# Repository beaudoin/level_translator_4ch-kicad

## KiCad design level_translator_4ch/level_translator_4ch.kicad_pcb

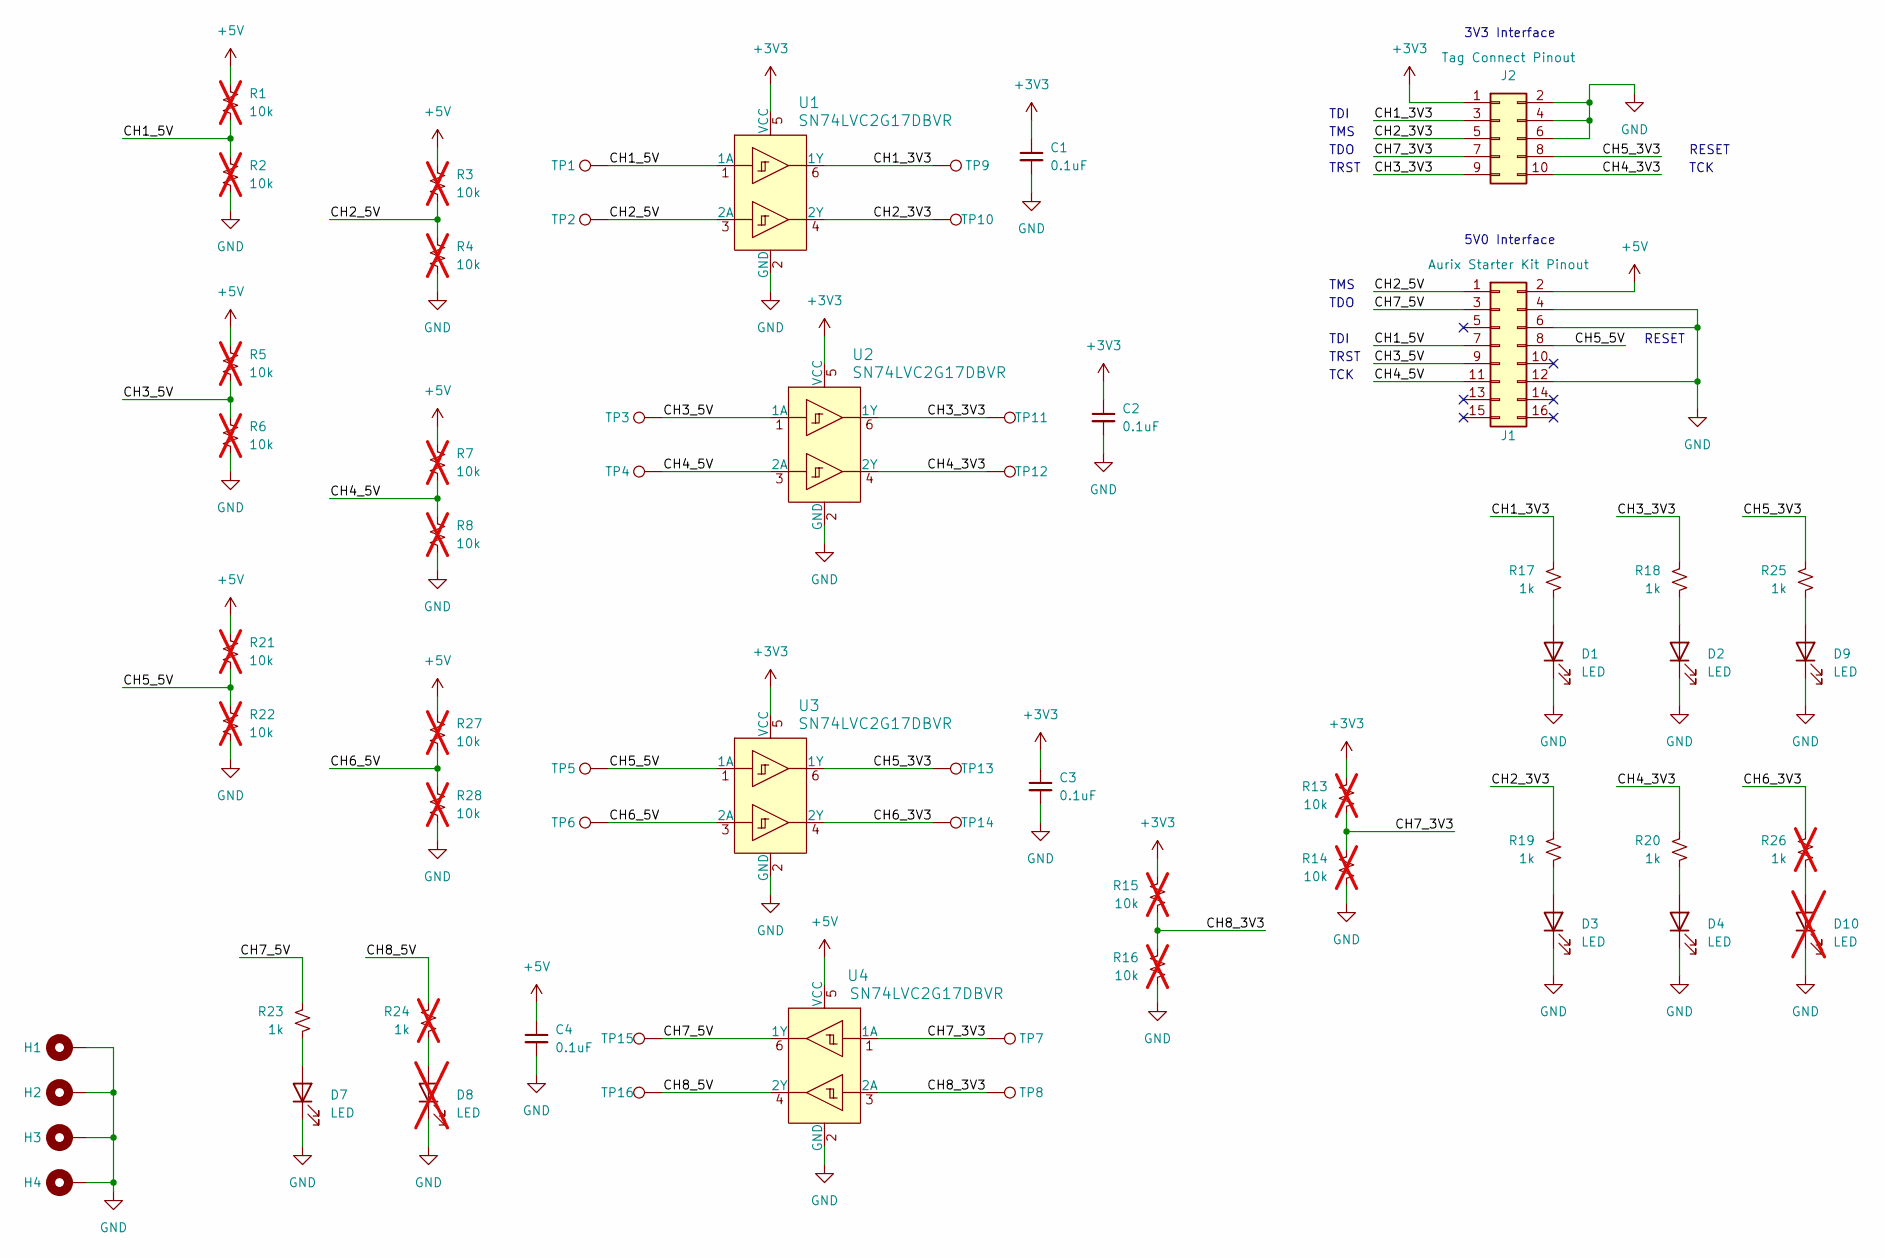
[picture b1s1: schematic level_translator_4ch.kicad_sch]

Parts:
C1, C2, C3, C4: 0.1uF; C_0603_1608Metric_Pad1.08x0.95mm_HandSolder
D1, D2, D3, D4, D7, D9: LED; LED_0603_1608Metric
D8, D10: LED; LED_0603_1608Metric; not fitted
H1, H2, H3, H4: MountingHole_Pad; MountingHole_3.2mm_M3_Pad
J1: Aurix Starter Kit Pinout; PinHeader_2x08_P2.54mm_Vertical
J2: Tag Connect Pinout; PinHeader_2x05_P2.54mm_Vertical
R1, R2, R3, R4, R5, R6, R7, R8, R13, R14, R15, R16, R21, R22, R27, R28: 10k; R_0603_1608Metric; not fitted
R17, R18, R19, R20, R23, R25: 1k; R_0603_1608Metric
R24, R26: 1k; R_0603_1608Metric; not fitted
TP1, TP2, TP3, TP4, TP5, TP6, TP7, TP8, TP9, TP10, TP11, TP12, TP13, TP14, TP15, TP16: TestPoint; TestPoint_Pad_D1.5mm
U1, U2, U3, U4: SN74LVC2G17DBVR; SOT-23-6; MPN SN74LVC2G17DBVR

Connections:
+3V3: C1.1, C2.1, C3.1, J2.1, R13.1, R15.1, U1.5 (VCC), U2.5 (VCC), U3.5 (VCC)
+5V: C4.1, J1.2, R1.1, R3.1, R5.1, R7.1, R21.1, R27.1, U4.5 (VCC)
/CH1_3V3: J2.3, R17.1, TP9.1, U1.6 (1Y)
/CH1_5V: J1.7, R1.2, R2.1, TP1.1, U1.1 (1A)
/CH2_3V3: J2.5, R19.1, TP10.1, U1.4 (2Y)
/CH2_5V: J1.1, R3.2, R4.1, TP2.1, U1.3 (2A)
/CH3_3V3: J2.9, R18.1, TP11.1, U2.6 (1Y)
/CH3_5V: J1.9, R5.2, R6.1, TP3.1, U2.1 (1A)
/CH4_3V3: J2.10, R20.1, TP12.1, U2.4 (2Y)
/CH4_5V: J1.11, R7.2, R8.1, TP4.1, U2.3 (2A)
/CH5_3V3: J2.8, R25.1, TP13.1, U3.6 (1Y)
/CH5_5V: J1.8, R21.2, R22.1, TP5.1, U3.1 (1A)
/CH6_3V3: R26.1, TP14.1, U3.4 (2Y)
/CH6_5V: R27.2, R28.1, TP6.1, U3.3 (2A)
/CH7_3V3: J2.7, R13.2, R14.1, TP7.1, U4.1 (1A)
/CH7_5V: J1.3, R23.1, TP15.1, U4.6 (1Y)
/CH8_3V3: R15.2, R16.1, TP8.1, U4.3 (2A)
/CH8_5V: R24.1, TP16.1, U4.4 (2Y)
GND: C1.2, C2.2, C3.2, C4.2, D1.1 (K), D2.1 (K), D3.1 (K), D4.1 (K), D7.1 (K), D8.1 (K), D9.1 (K), D10.1 (K), H1.1, H2.1, H3.1, H4.1, J1.4, J1.6, J1.12, J2.2, J2.4, J2.6, R2.2, R4.2, R6.2, R8.2, R14.2, R16.2, R22.2, R28.2, U1.2 (GND), U2.2 (GND), U3.2 (GND), U4.2 (GND)
unnamed: D1.2 (A), R17.2
unnamed: D2.2 (A), R18.2
unnamed: D3.2 (A), R19.2
unnamed: D4.2 (A), R20.2
unnamed: D7.2 (A), R23.2
unnamed: D8.2 (A), R24.2
unnamed: D9.2 (A), R25.2
unnamed: D10.2 (A), R26.2

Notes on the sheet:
TDI
3V3 Interface
RESET
TMS
TCK
TDO
TRST
5V0 Interface

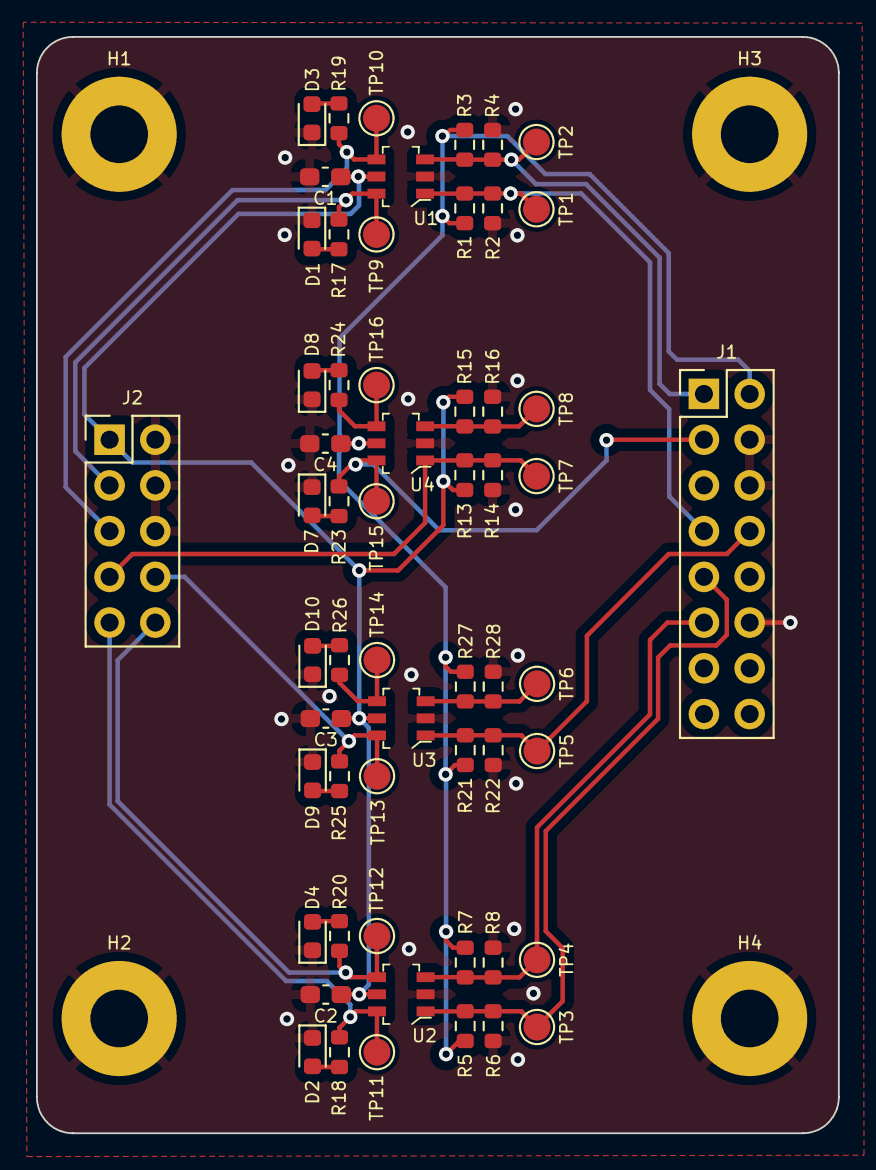
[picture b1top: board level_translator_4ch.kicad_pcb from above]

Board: 2 copper layers, 44.6 x 60.9 mm, 62 parts (0 on the bottom side), 27 nets.

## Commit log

2024-06-10 Initial check-in
2024-06-21 Added schematic pdf
2024-06-24 Added 3D printed shell enclosure for the 4 channel level translator board.
